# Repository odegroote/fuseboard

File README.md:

# fuseboard
pcb design for a 1s8p 18650 batterycell

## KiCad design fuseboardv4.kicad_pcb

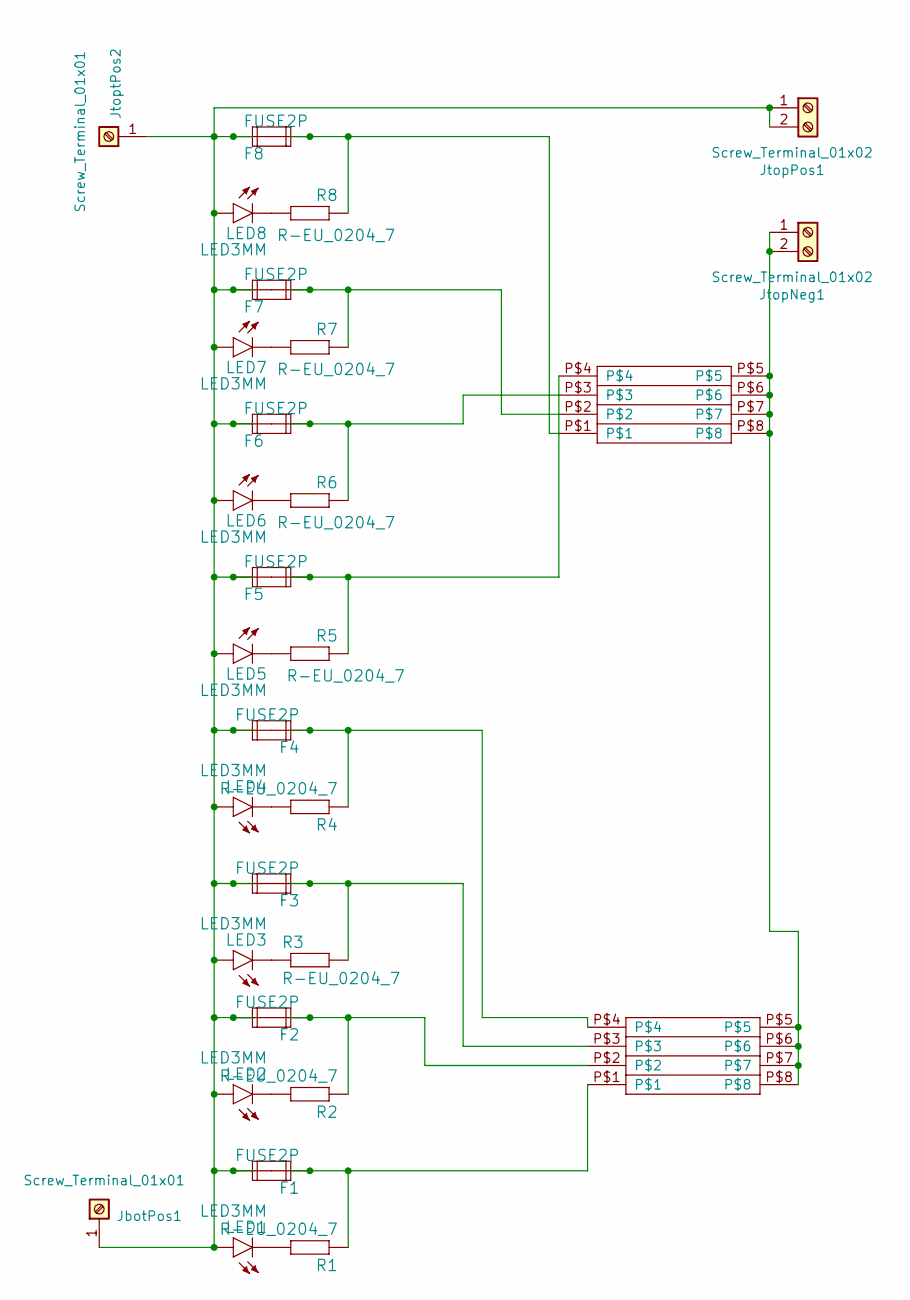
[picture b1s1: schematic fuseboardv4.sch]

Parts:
F1, F2, F3, F4, F5, F6, F7, F8: FUSE2P; FUSE1
JbotPos1: Screw_Terminal_01x01; LSK 271
JtopNeg1: Screw_Terminal_01x02; TerminalBlock_MetzConnect_Type175_RT02702HBLC_Pitch7.50mm
JtopPos1: Screw_Terminal_01x02; TerminalBlock_MetzConnect_Type175_RT02702HBLC_Pitch7.50mm
JtoptPos2: Screw_Terminal_01x01; LSK 271
LED1, LED2, LED3, LED4, LED5, LED6, LED7, LED8: LED3MM
R1, R2, R3, R4, R5, R6, R7, R8: R-EU_0204_7; 0204_7
U$1, U$2: E1A1BATTERYHOLDERVERSION1; E1A14S

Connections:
unnamed: F1.1A, F1.1B, R1.1, U$1.P$1
unnamed: F1.2A, F1.2B, F2.2A, F2.2B, F3.2A, F3.2B, F4.2A, F4.2B, F5.1A, F5.1B, F6.1A, F6.1B, F7.1A, F7.1B, F8.1A, F8.1B, JbotPos1.1, JtopPos1.1, JtopPos1.2, JtoptPos2.1, LED1.A, LED2.A, LED3.A, LED4.A, LED5.A, LED6.A, LED7.A, LED8.A
unnamed: F2.1A, F2.1B, R2.1, U$1.P$2
unnamed: F3.1A, F3.1B, R3.2, U$1.P$3
unnamed: F4.1A, F4.1B, R4.1, U$1.P$4
unnamed: F5.2A, F5.2B, R5.1, U$2.P$4
unnamed: F6.2A, F6.2B, R6.1, U$2.P$3
unnamed: F7.2A, F7.2B, R7.1, U$2.P$2
unnamed: F8.2A, F8.2B, R8.1, U$2.P$1
unnamed: JtopNeg1.1, JtopNeg1.2, U$1.P$5, U$1.P$6, U$1.P$7, U$1.P$8, U$2.P$5, U$2.P$6, U$2.P$7, U$2.P$8
unnamed: LED1.K (C), R1.2
unnamed: LED2.K (C), R2.2
unnamed: LED3.K (C), R3.1
unnamed: LED4.K (C), R4.2
unnamed: LED5.K (C), R5.2
unnamed: LED6.K (C), R6.2
unnamed: LED7.K (C), R7.2
unnamed: LED8.K (C), R8.2

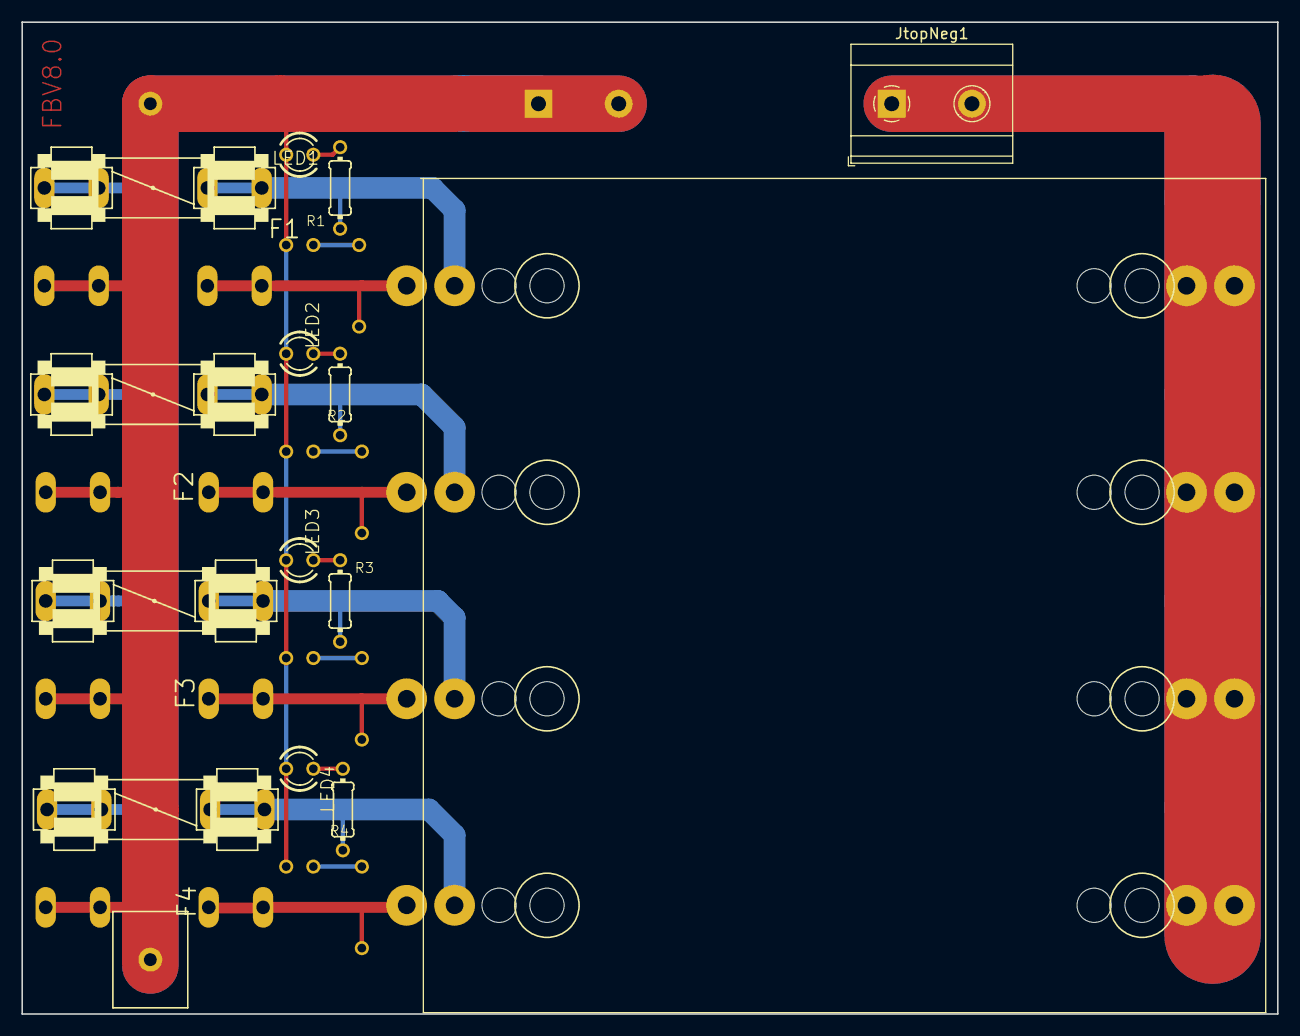
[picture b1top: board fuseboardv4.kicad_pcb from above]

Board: 2 copper layers, 117.4 x 92.7 mm, 30 parts (0 on the bottom side), 18 nets.
